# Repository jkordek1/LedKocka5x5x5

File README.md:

# LedKocka5x5x5

## What is it?
Just another 125 LED cube powered by ATmega16 microcontroller and HC595 shift registers.

## Video
Video of it in action: https://www.youtube.com/watch?v=YpSFf-s8Nvs

## Problems
Project BOM is not optimal. Due to electronic components shortage, "on-hand" available components were used.

## Images

## Project folder structure
    .
    ├── ...
    ├── Code                    # C code for microcontroller
    ├── Enclosure               # 3D files and images of enclosure
    ├── Images                  # Project images folder
    ├── Output files            # Gerber files folder
    ├── KiCad files             # Main folder
    │   ├── LED_Cube_5X5X5      # First KiCAD project folder
    │   └── LED_Cube_5X5X5_PCB2 # Second KiCAD project folder
    └── ...

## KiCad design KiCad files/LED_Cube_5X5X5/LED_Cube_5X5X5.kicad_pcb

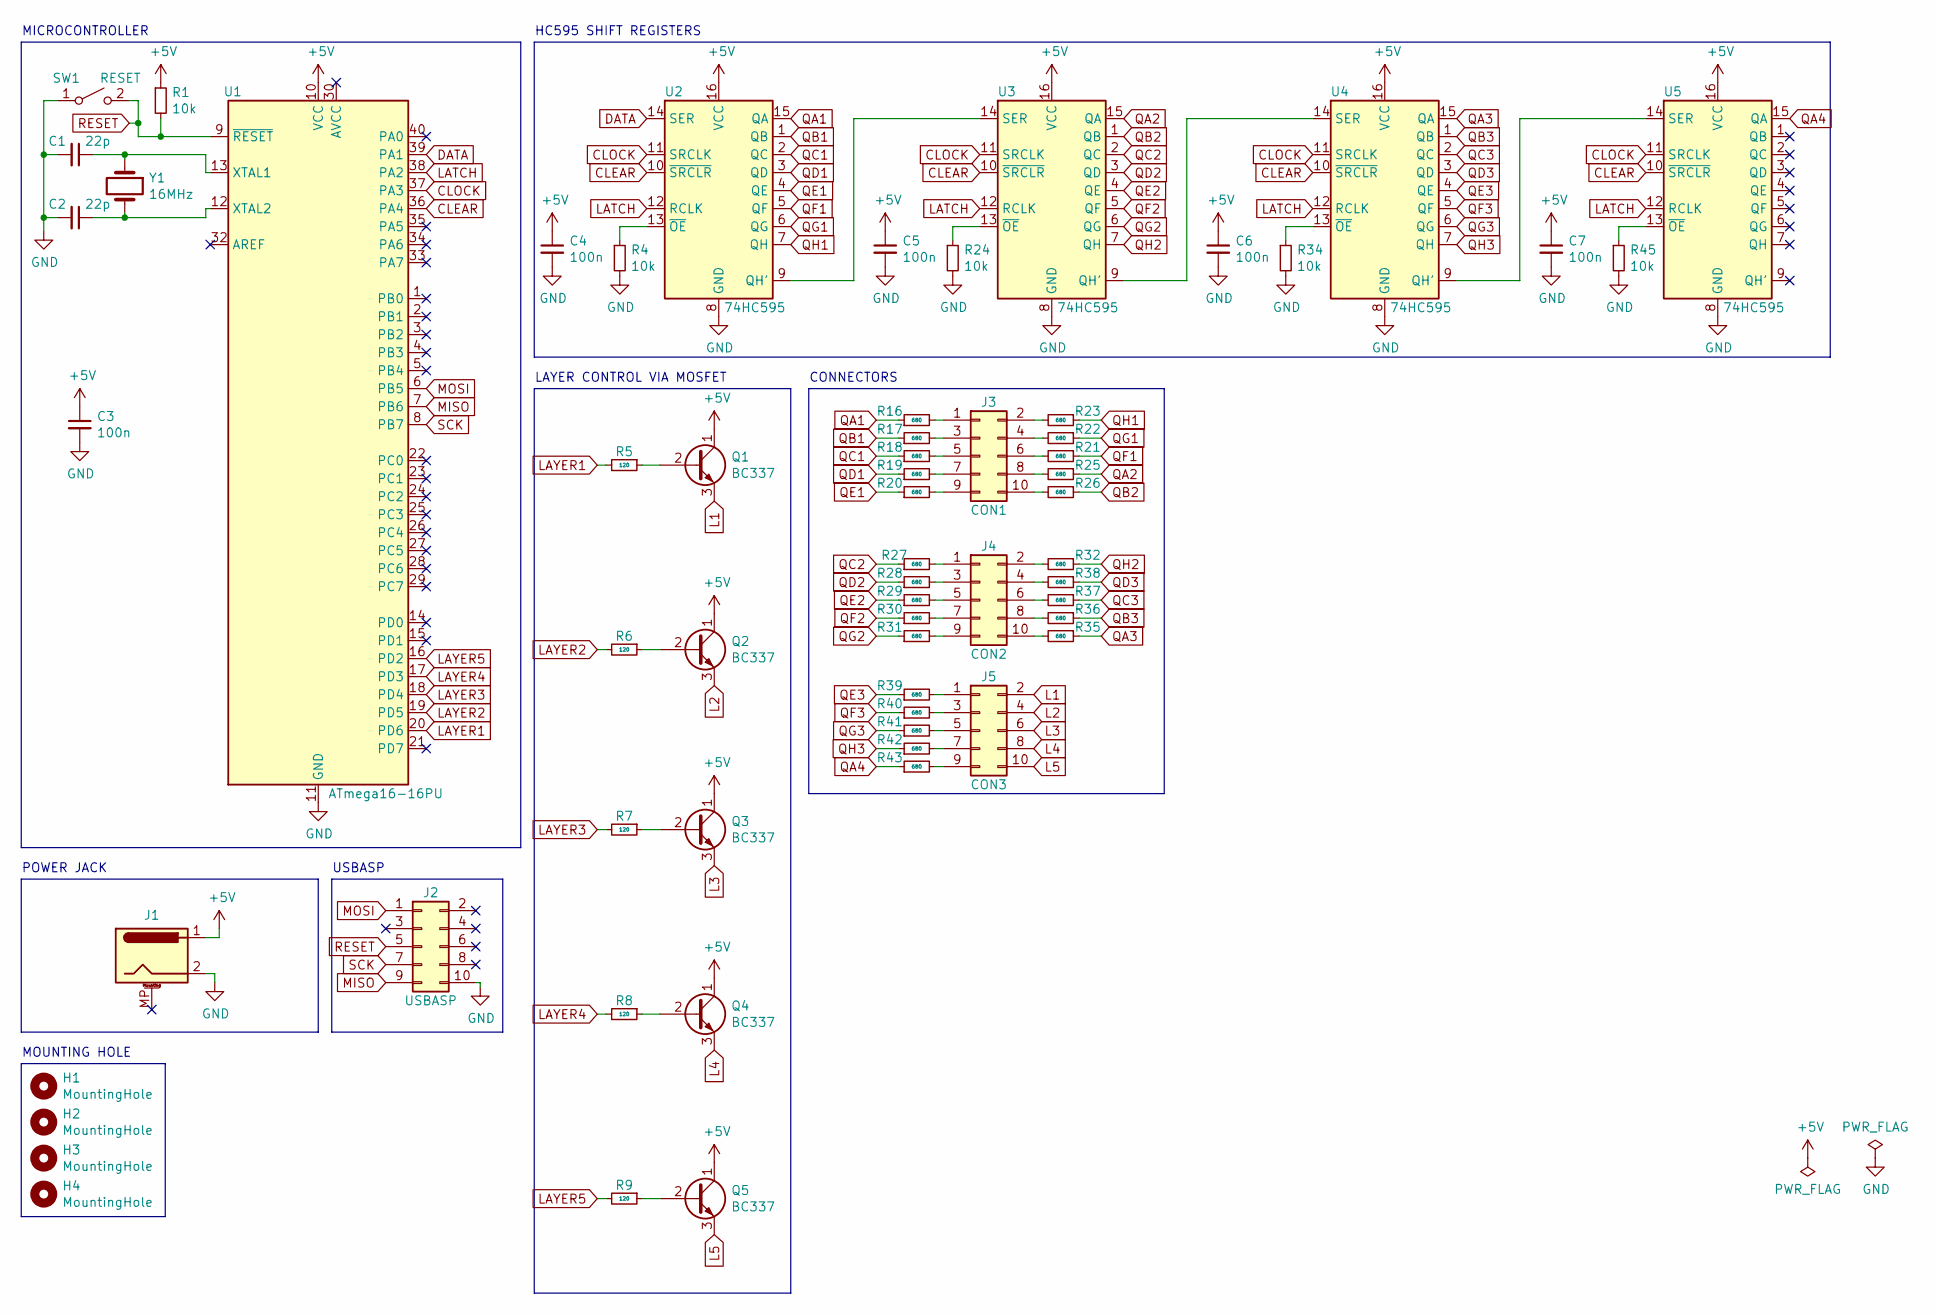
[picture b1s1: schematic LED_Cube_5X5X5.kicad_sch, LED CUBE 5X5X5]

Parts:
C1, C2: 22p; C_Disc_D3.0mm_W1.6mm_P2.50mm
C3, C4, C5, C6, C7: 100n; CP_Radial_Tantal_D5.0mm_P5.00mm
H1, H2, H3, H4: MountingHole; MountingHole_3.2mm_M3_Pad
J1: Barrel_Jack_MountingPin; BarrelJack_Wuerth_6941xx301002
J2: USBASP; IDC-Header_2x05_P2.54mm_Horizontal
J3: CON1; IDC-Header_2x05_P2.54mm_Vertical
J4: CON2; IDC-Header_2x05_P2.54mm_Vertical
J5: CON3; IDC-Header_2x05_P2.54mm_Vertical
Q1, Q2, Q3, Q4, Q5: BC337; TO-92_Inline
R1, R4, R24, R34, R45: 10k; R_Axial_DIN0207_L6.3mm_D2.5mm_P7.62mm_Horizontal
R5, R6, R7, R8, R9: 120; R_Axial_DIN0207_L6.3mm_D2.5mm_P7.62mm_Horizontal
R16, R17, R18, R19, R20, R21, R22, R23, R25, R26, R27, R28, R29, R30, R31, R32, R35, R36, R37, R38, R39, R40, R41, R42, R43: 680; R_Axial_DIN0207_L6.3mm_D2.5mm_P7.62mm_Horizontal
SW1: RESET; SW_Tactile_SPST_Angled_PTS645Vx39-2LFS
U1: ATmega16-16PU; DIP-40_W15.24mm_Socket_LongPads
U2, U3, U4, U5: 74HC595; DIP-16_W7.62mm_Socket_LongPads
Y1: 16MHz; Crystal_HC49-4H_Vertical

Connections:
+5V: C3.1, C4.1, C5.1, C6.1, C7.1, J1.1, Q1.1 (C), Q2.1 (C), Q3.1 (C), Q4.1 (C), Q5.1 (C), R1.1, U1.10 (VCC), U2.16 (VCC), U3.16 (VCC), U4.16 (VCC), U5.16 (VCC)
CLEAR: U1.36 (PA4), U2.10 (~SRCLR), U3.10 (~SRCLR), U4.10 (~SRCLR), U5.10 (~SRCLR)
CLOCK: U1.37 (PA3), U2.11 (SRCLK), U3.11 (SRCLK), U4.11 (SRCLK), U5.11 (SRCLK)
DATA: U1.39 (PA1), U2.14 (SER)
GND: C1.2, C2.2, C3.2, C4.2, C5.2, C6.2, C7.2, J1.2, J2.10, R4.2, R24.2, R34.2, R45.2, SW1.1 (A), U1.11 (GND), U1.31 (GND), U2.8 (GND), U3.8 (GND), U4.8 (GND), U5.8 (GND)
L1: J5.2, Q1.3 (E)
L2: J5.4, Q2.3 (E)
L3: J5.6, Q3.3 (E)
L4: J5.8, Q4.3 (E)
L5: J5.10, Q5.3 (E)
LATCH: U1.38 (PA2), U2.12 (RCLK), U3.12 (RCLK), U4.12 (RCLK), U5.12 (RCLK)
LAYER1: R5.2, U1.20 (PD6)
LAYER2: R6.2, U1.19 (PD5)
LAYER3: R7.2, U1.18 (PD4)
LAYER4: R8.2, U1.17 (PD3)
LAYER5: R9.2, U1.16 (PD2)
MISO: J2.9, U1.7 (PB6)
MOSI: J2.1, U1.6 (PB5)
unnamed: C1.1, U1.13 (XTAL1), Y1.1
unnamed: C2.1, U1.12 (XTAL2), Y1.2
unnamed: J3.1, R16.2
unnamed: J3.2, R23.2
unnamed: J3.3, R17.2
unnamed: J3.4, R22.2
unnamed: J3.5, R18.2
unnamed: J3.6, R21.2
unnamed: J3.7, R19.2
unnamed: J3.8, R25.2
unnamed: J3.9, R20.2
unnamed: J3.10, R26.2
unnamed: J4.1, R27.2
unnamed: J4.2, R32.2
unnamed: J4.3, R28.2
unnamed: J4.4, R38.2
unnamed: J4.5, R29.2
unnamed: J4.6, R37.2
unnamed: J4.7, R30.2
unnamed: J4.8, R36.2
unnamed: J4.9, R31.2
unnamed: J4.10, R35.2
unnamed: J5.1, R39.2
unnamed: J5.3, R40.2
unnamed: J5.5, R41.2
unnamed: J5.7, R42.2
unnamed: J5.9, R43.2
unnamed: Q1.2 (B), R5.1
unnamed: Q2.2 (B), R6.1
unnamed: Q3.2 (B), R7.1
unnamed: Q4.2 (B), R8.1
unnamed: Q5.2 (B), R9.1
unnamed: R4.1, U2.13 (~OE)
unnamed: R24.1, U3.13 (~OE)
unnamed: R34.1, U4.13 (~OE)
unnamed: R45.1, U5.13 (~OE)
unnamed: U2.9 (QH'), U3.14 (SER)
unnamed: U3.9 (QH'), U4.14 (SER)
unnamed: U4.9 (QH'), U5.14 (SER)
QA1: R16.1, U2.15 (QA)
QA2: R25.1, U3.15 (QA)
QA3: R35.1, U4.15 (QA)
QA4: R43.1, U5.15 (QA)
QB1: R17.1, U2.1 (QB)
QB2: R26.1, U3.1 (QB)
QB3: R36.1, U4.1 (QB)
QC1: R18.1, U2.2 (QC)
QC2: R27.1, U3.2 (QC)
QC3: R37.1, U4.2 (QC)
QD1: R19.1, U2.3 (QD)
QD2: R28.1, U3.3 (QD)
QD3: R38.1, U4.3 (QD)
QE1: R20.1, U2.4 (QE)
QE2: R29.1, U3.4 (QE)
QE3: R39.1, U4.4 (QE)
QF1: R21.1, U2.5 (QF)
QF2: R30.1, U3.5 (QF)
QF3: R40.1, U4.5 (QF)
QG1: R22.1, U2.6 (QG)
QG2: R31.1, U3.6 (QG)
QG3: R41.1, U4.6 (QG)
QH1: R23.1, U2.7 (QH)
QH2: R32.1, U3.7 (QH)
QH3: R42.1, U4.7 (QH)
RESET: J2.5, R1.2, SW1.2 (B), U1.9 (~RESET)
SCK: J2.7, U1.8 (PB7)

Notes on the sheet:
POWER JACK
USBASP
HC595 SHIFT REGISTERS
LAYER CONTROL VIA MOSFET
MOUNTING HOLE
MICROCONTROLLER
CONNECTORS

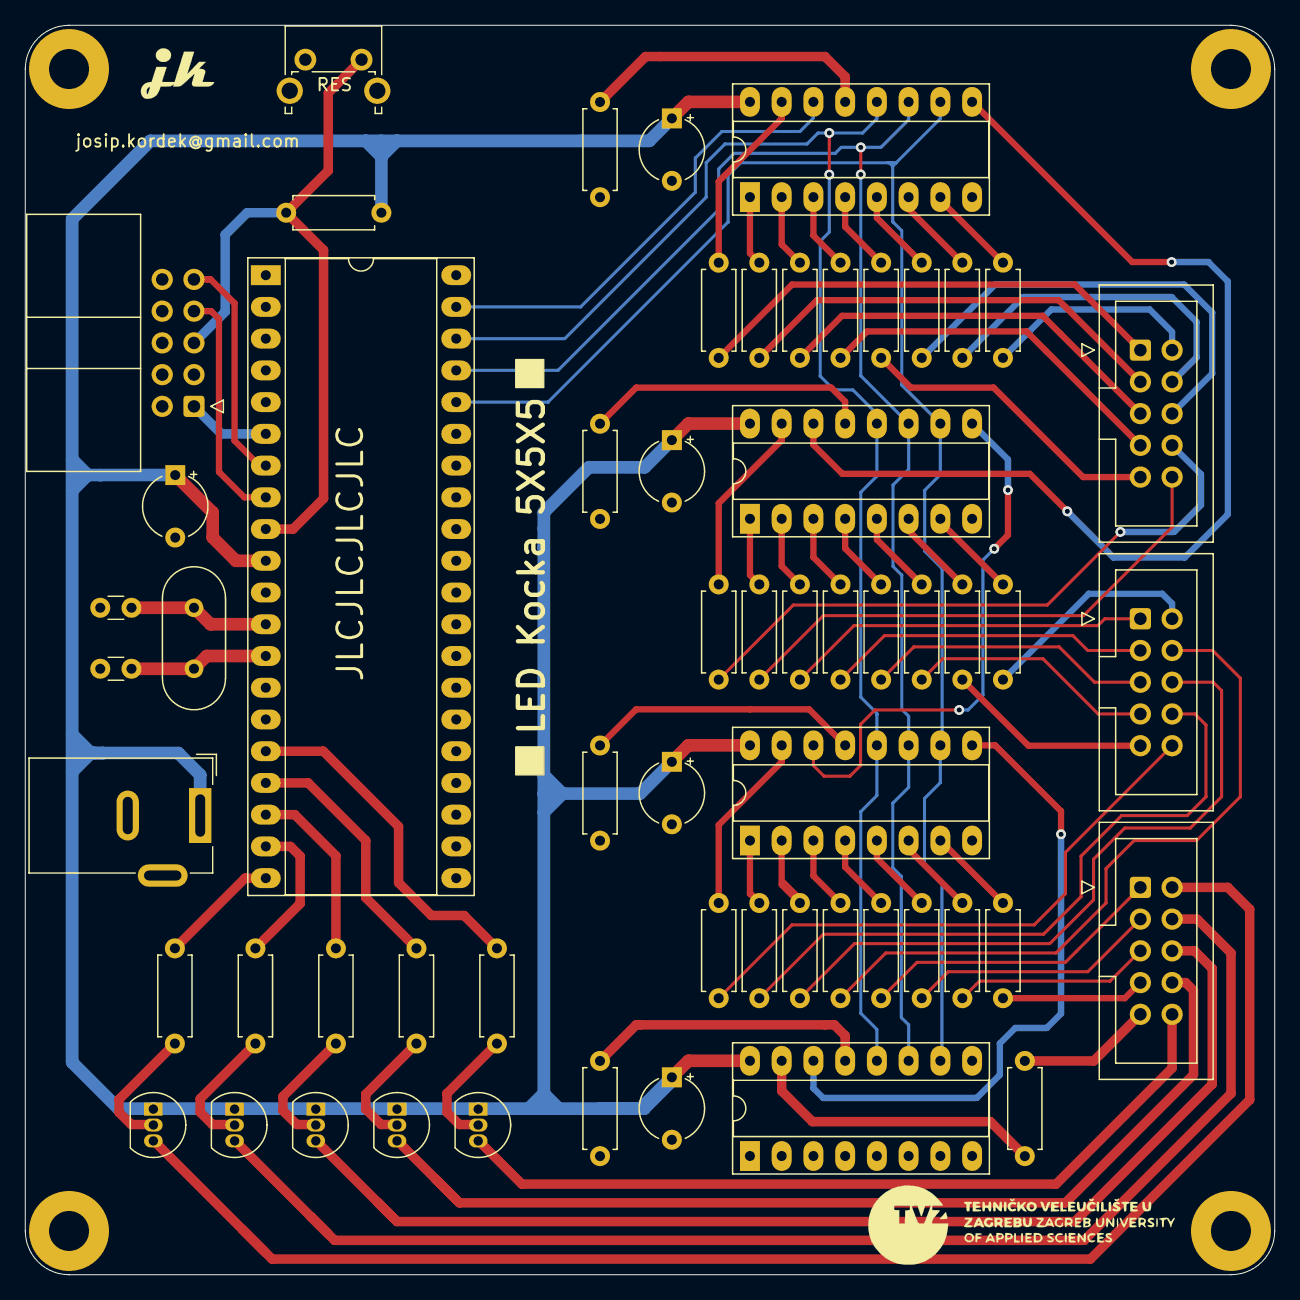
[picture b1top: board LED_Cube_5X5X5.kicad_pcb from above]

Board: 2 copper layers, 100.0 x 100.0 mm, 63 parts (0 on the bottom side), 84 nets.

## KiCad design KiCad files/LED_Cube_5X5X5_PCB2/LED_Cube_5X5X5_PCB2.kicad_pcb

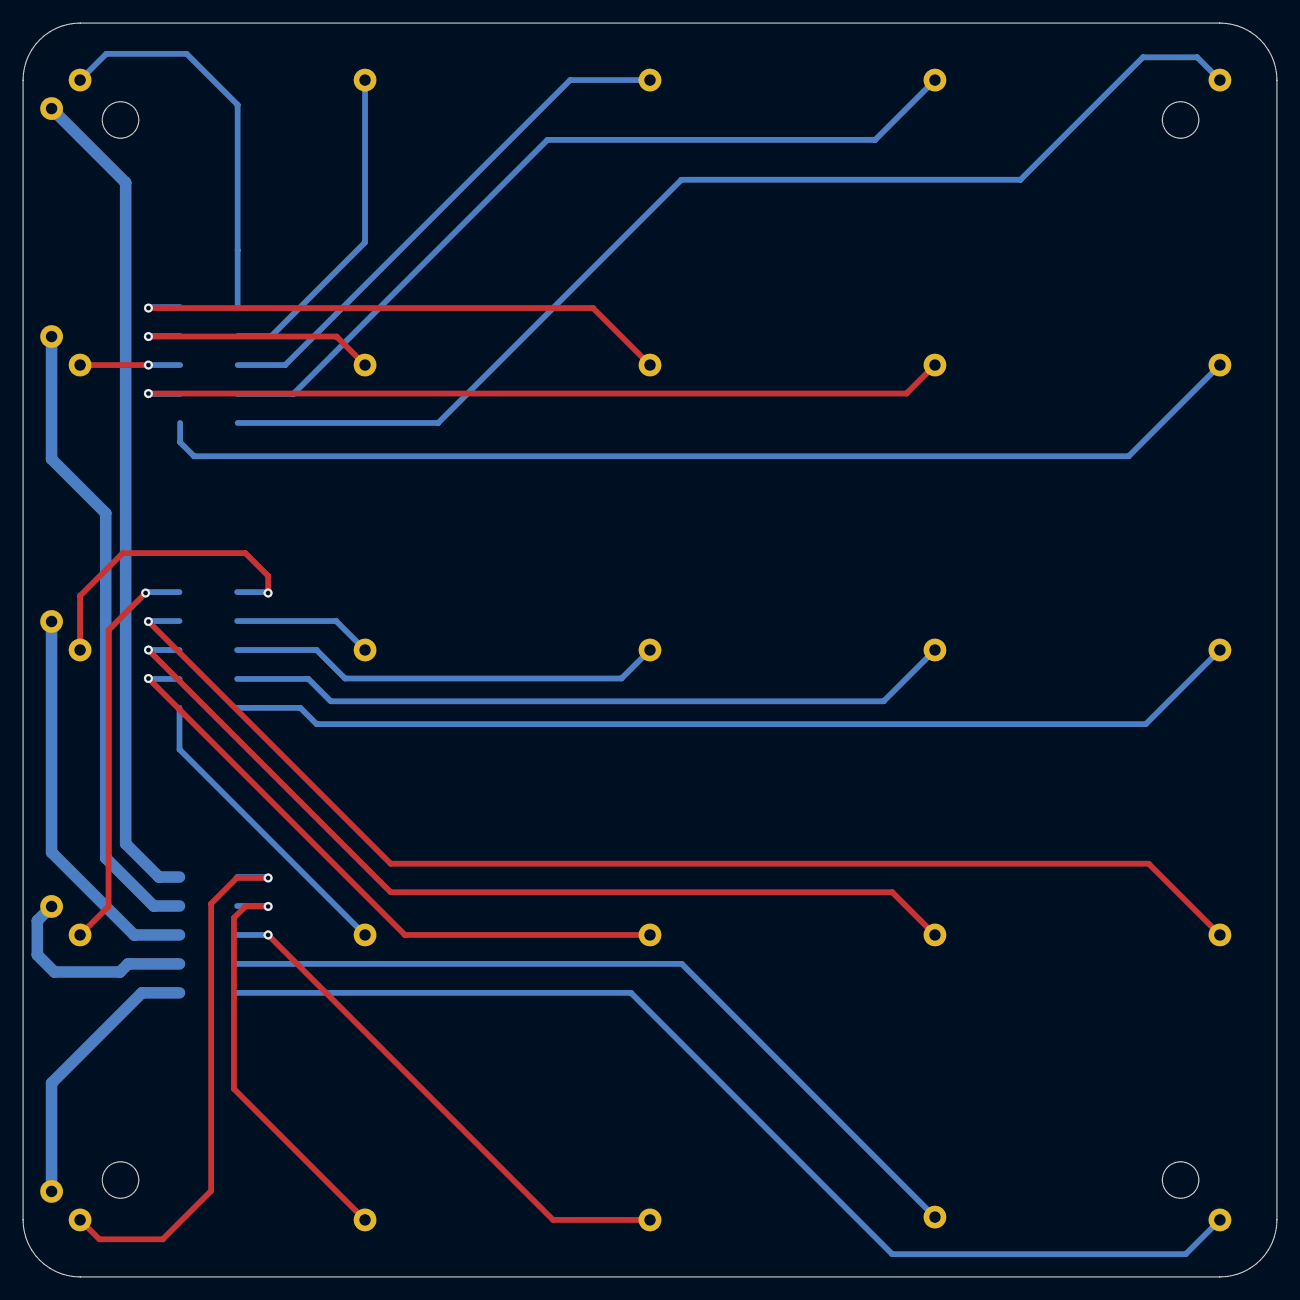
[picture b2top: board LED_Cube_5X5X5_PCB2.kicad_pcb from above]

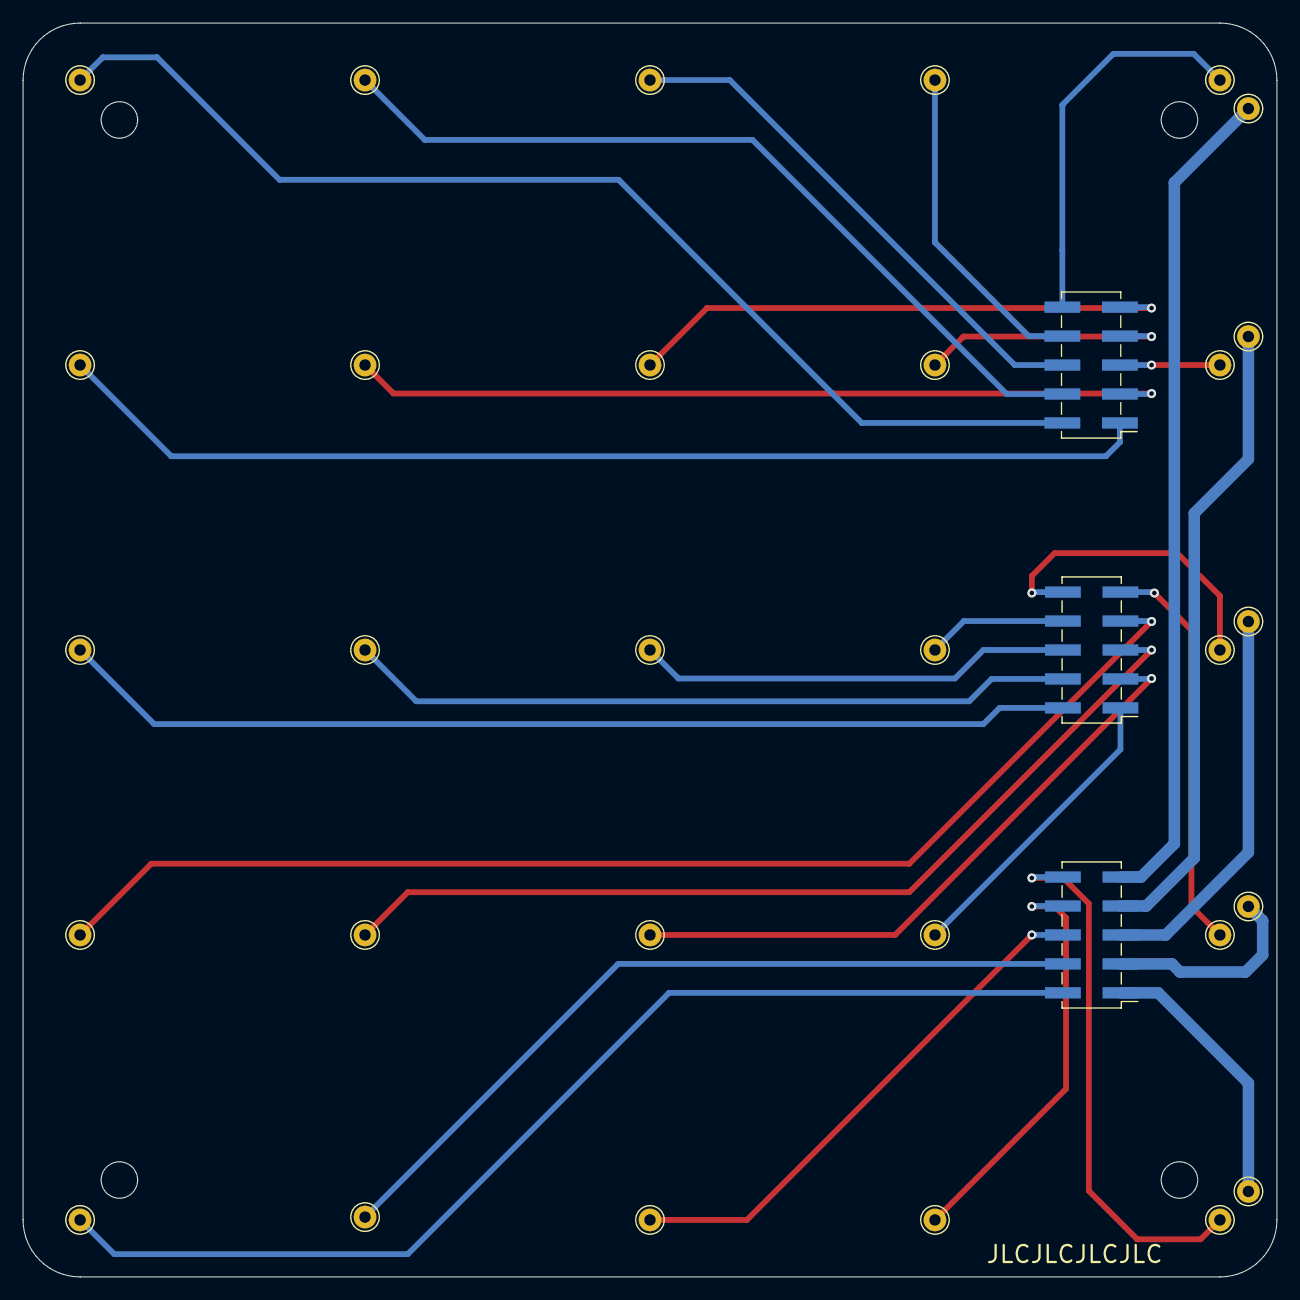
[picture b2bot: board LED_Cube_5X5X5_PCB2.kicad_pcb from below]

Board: 2 copper layers, 110.0 x 110.0 mm, 37 parts (33 on the bottom side), 30 nets.

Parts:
H1, H2, H3, H4: MountingHole; MountingHole_3.2mm_M3
J1, J2, J3, J4, J5, J6, J7, J8, J9, J10, J11, J12, J13, J14, J15, J16, J17, J18, J19, J20, J21, J22, J23, J24, J25, J26, J27, J28, J29, J30: Conn_01x01; Pin_D1.0mm_L10.0mm
J31, J32, J33: Conn_02x05_Odd_Even; PinHeader_2x05_P2.54mm_Vertical_SMD

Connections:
unnamed: J1.1, J31.10
unnamed: J2.1, J31.8
unnamed: J3.1, J31.6
unnamed: J10.1, J31.1
unnamed: J11.1, J32.10
unnamed: J12.1, J32.8
unnamed: J13.1, J32.6
unnamed: J14.1, J32.4
unnamed: J15.1, J32.2
unnamed: J16.1, J32.9
unnamed: J17.1, J32.1
unnamed: J18.1, J32.3
unnamed: J19.1, J32.5
unnamed: J20.1, J32.7
unnamed: J21.1, J33.10
unnamed: J22.1, J33.8
unnamed: J23.1, J33.6
unnamed: J24.1, J33.4
unnamed: J25.1, J33.2
unnamed: J26.1, J33.9
unnamed: J27.1, J33.7
unnamed: J28.1, J33.5
unnamed: J29.1, J33.3
unnamed: J30.1, J33.1
unnamed: J5.1, J31.2
unnamed: J9.1, J31.3
unnamed: J4.1, J31.4
unnamed: J6.1, J31.5
unnamed: J7.1, J31.7
unnamed: J8.1, J31.9

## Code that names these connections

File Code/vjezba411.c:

#ifdef F_CPU
#undef F_CPU
#define F_CPU 16000000l
#endif

#include "AVR lib/AVR_lib.h"
#include <avr/io.h>
#include <util/delay.h>
#include <avr/interrupt.h>
int trenutni_sloj = 1;
int trenutni_stupac = 6;
int slovo = 1;

int MOD = 1;

#define DATA PA1
#define CLOCK PA3
#define LATCH PA2
#define CLEAR PA4

#define LAYER1 PD2
#define LAYER2 PD3
#define LAYER3 PD4
#define LAYER4 PD5
#define LAYER5 PD6

int T[5][5] = {
	{0, 0, 0, 0, 0},
	{1, 1, 0, 1, 1},
	{1, 1, 0, 1, 1},
	{1, 1, 0, 1, 1},
	{1, 1, 0, 1, 1}
	};
	
int V[5][5] = {
	{0, 1, 1, 1, 0},
	{0, 1, 1, 1, 0},
	{1, 0, 1, 0, 1},
	{1, 0, 1, 0, 1},
	{1, 1, 0, 1, 1}
};

int Z[5][5] = {
	{0, 0, 0, 0, 0},
	{1, 0, 1, 1, 1},
	{1, 1, 0, 1, 1},
	{1, 1, 1, 0, 1},
	{0, 0, 0, 0, 0}
};

int K[5][5] = {
	{0, 1, 1, 1, 0},
	{1, 0, 1, 1, 0},
	{1, 1, 0, 0, 0},
	{1, 0, 1, 1, 0},
	{0, 1, 1, 1, 0}
};

int I[5][5] = {
	{1, 1, 0, 1, 1},
	{1, 1, 1, 1, 1},
	{1, 1, 0, 1, 1},
	{1, 1, 0, 1, 1},
	{1, 1, 0, 1, 1}
};

int R[5][5] = {
	{1, 1, 0, 0, 0},
	{1, 0, 1, 1, 0},
	{1, 1, 0, 0, 0},
	{1, 1, 0, 1, 0},
	{1, 0, 1, 1, 0}
};

int prazno[5][5] = {
	{1, 1, 1, 1, 1},
	{1, 1, 1, 1, 1},
	{1, 1, 1, 1, 1},
	{1, 1, 1, 1, 1},
	{1, 1, 1, 1, 1}
};
			
void all_off(){
			for(int j = 0; j < 25; j++){
				set_port(PORTA, DATA, 1);
				TOGGLE_PORT(PORTA, CLOCK); //1
				TOGGLE_PORT(PORTA, CLOCK); //0
			}

	TOGGLE_PORT(PORTA, LATCH); //1
	TOGGLE_PORT(PORTA, LATCH); //0
	
}	


void sloj(int x){
	
	switch(x){
		
		case 1:
		output_port(DDRD, LAYER1);
		set_port(PORTD, LAYER1, 1);
		output_port(DDRD, LAYER5);
		set_port(PORTD, LAYER5, 0);
		break;
		
		case 2:
		output_port(DDRD, LAYER2);
		set_port(PORTD, LAYER2, 1);
		output_port(DDRD, LAYER1);
		set_port(PORTD, LAYER1, 0);
		break;
		
		case 3:
		output_port(DDRD, LAYER3);
		set_port(PORTD, LAYER3, 1);
		output_port(DDRD, LAYER2);
		set_port(PORTD, LAYER2, 0);
		break;
		
		case 4:
		output_port(DDRD, LAYER4);
		set_port(PORTD, LAYER4, 1);
		output_port(DDRD, LAYER3);
		set_port(PORTD, LAYER3, 0);
		break;
		
		case 5:
		output_port(DDRD, LAYER5);
		set_port(PORTD, LAYER5, 1);
		output_port(DDRD, LAYER4);
		set_port(PORTD, LAYER4, 0);
		break;
		
	}

}

ISR(TIMER0_OVF_vect){ // prekidna rutina za timer0
	TCNT0 = 200; // po? etna vrijednost registra
	
	
	sloj(trenutni_sloj);
	
	for(int j = 0; j < (trenutni_stupac-1)*5; j++){
		set_port(PORTA, DATA, 1);
		TOGGLE_PORT(PORTA, CLOCK); //1
		TOGGLE_PORT(PORTA, CLOCK); //0
	}
	
	for(int i = 0; i < 5; i++){
		if(slovo == 1){
		set_port(PORTA, DATA, T[trenutni_sloj - 1][i]);
		}
		else if(slovo == 2){
			set_port(PORTA, DATA, V[trenutni_sloj - 1][i]);
		}
		else if(slovo == 3){
			set_port(PORTA, DATA, Z[trenutni_sloj - 1][i]);
		}
		else if(slovo == 4){
			set_port(PORTA, DATA, prazno[trenutni_sloj - 1][i]);
		}
		else if(slovo == 5){
			set_port(PORTA, DATA, K[trenutni_sloj - 1][i]);
		}
		else if(slovo == 6){
			set_port(PORTA, DATA, I[trenutni_sloj - 1][i]);
		}
		else if(slovo == 7){
			set_port(PORTA, DATA, R[trenutni_sloj - 1][i]);
		}
		else if(slovo == 8){
			set_port(PORTA, DATA, T[trenutni_sloj - 1][i]);
		}
		else if(slovo == 9){
			set_port(PORTA, DATA, prazno[trenutni_sloj - 1][i]);
		}	
		TOGGLE_PORT(PORTA, CLOCK); //1
		TOGGLE_PORT(PORTA, CLOCK); //0
	}
	for(int j = 0; j < 25 - trenutni_stupac*5; j++){
		set_port(PORTA, DATA, 1);
		TOGGLE_PORT(PORTA, CLOCK); //1
		TOGGLE_PORT(PORTA, CLOCK); //0
	}
	
	TOGGLE_PORT(PORTA, LATCH); //1
	TOGGLE_PORT(PORTA, LATCH); //0
	trenutni_sloj++;

	if(trenutni_sloj == 6)	trenutni_sloj = 1;

	
}
void inicijalizacija(){
	
	TCCR0 |= (0 << WGM01 ) | (0 << WGM00 ) ; // normalan na?in rada
	TCCR0 |= (1 << CS02 ) | (0 << CS01 ) | (1 << CS00 ) ; // F_CPU / 1024
	TIMSK |= (1 << TOIE0 ) ; // omoguæi prekid TOV0
	//DATA, CLOCK i LATCH pinovi postavljeni kao izlazni
	DDRA |= (1 << DATA) | (1 << CLOCK) | (1 << LATCH);
	
	//pinovi slojeva postavljeni kao izlazni
	DDRD |= (1 << LAYER1) | (1 << LAYER2) | (1 << LAYER3) | (1 << LAYER4) | (1 << LAYER5);
	
	//DATA 0
	set_port(PORTA, DATA, 0);

	DDRA |= (1 << CLEAR);
	PORTA |= (1 << CLEAR);
	
	TCNT0 = 25;
	
	all_off();
	
	sei();
}

int main(void){
		
	inicijalizacija();
	
	while(1){
	
	trenutni_stupac--;
	if (trenutni_stupac == 0) {
		slovo++;
		if (slovo == 10) slovo = 1;
		trenutni_stupac = 5;}
	
	_delay_ms(100);

}
	
	
return 0;
	
}

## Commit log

2021-10-02 Initial release
2021-10-02 Images
2021-10-02 Reduced image resolution
2021-10-02 Uređeno
2021-10-02 test
2021-10-02 enclosure
2021-10-04 Code added
2021-10-06 code v4
2022-01-25 Update .atsuo
    update
2022-02-09 PCB image
2022-02-09 Schematic
2022-02-09 gerber and bom
2022-02-10 3d model
